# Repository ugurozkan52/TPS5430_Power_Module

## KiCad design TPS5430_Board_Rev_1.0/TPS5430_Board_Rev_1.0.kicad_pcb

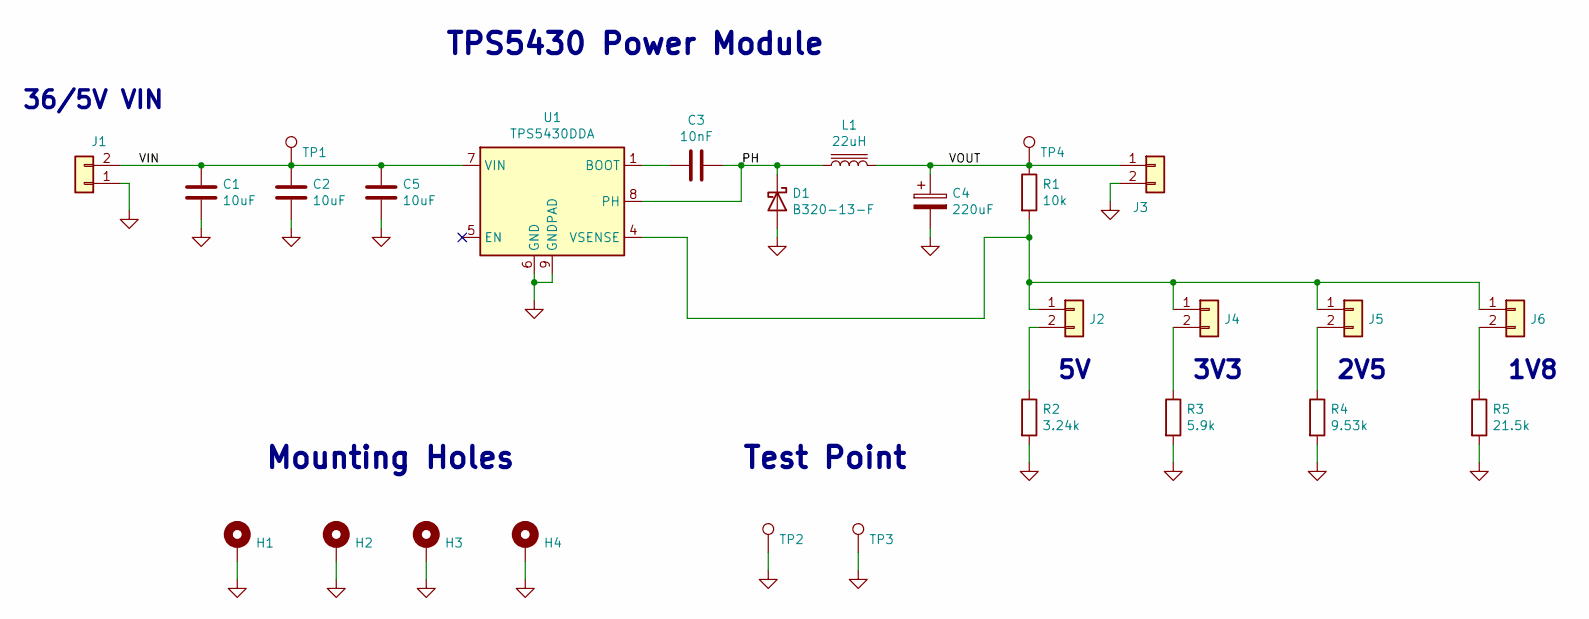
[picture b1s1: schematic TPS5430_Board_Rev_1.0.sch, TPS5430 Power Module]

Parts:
C1, C2, C5: 10uF; C_1210_3225Metric_Pad1.33x2.70mm_HandSolder; Manufacturer Part Number C3225X7R1H106M250AC
C3: 10nF; C_0805_2012Metric_Pad1.18x1.45mm_HandSolder; Manufacturer Part Number CC0805KRX7R9BB103
C4: 220uF; CP_Elec_6.3x5.9; Manufacturer Part Number 6SVPC330M
D1: B320-13-F; D_SMC_Handsoldering; Manufacturer Part Number B320-13-F
H1, H2, H3, H4: MountingHole_Pad; MountingHole_3.2mm_M3_Pad_Via
J1, J3: Conn_01x02; TerminalBlock_Phoenix_MPT-0,5-2-2.54_1x02_P2.54mm_Horizontal; Manufacturer Part Number OSTVN02A150
J2, J4, J5, J6: Conn_01x02; PinHeader_1x02_P2.54mm_Vertical; Manufacturer Part Number 77311-818-02LF
L1: 22uH; L_Wuerth_WE-PD-Typ-LS_Handsoldering; Manufacturer Part Number 7447709220
R1: 10k; R_0805_2012Metric_Pad1.20x1.40mm_HandSolder; Manufacturer Part Number ERJ-6ENF1002V
R2: 3.24k; R_0805_2012Metric_Pad1.20x1.40mm_HandSolder; Manufacturer Part Number ERJ-6ENF3241V
R3: 5.9k; R_0805_2012Metric_Pad1.20x1.40mm_HandSolder; Manufacturer Part Number ERJ-6ENF5901V
R4: 9.53k; R_0805_2012Metric_Pad1.20x1.40mm_HandSolder; Manufacturer Part Number ERJ-6ENF9531V
R5: 21.5k; R_0805_2012Metric_Pad1.20x1.40mm_HandSolder; Manufacturer Part Number ERJ-6ENF2152V
TP1, TP4: TestPoint; TestPoint_THTPad_2.5x2.5mm_Drill1.2mm; Manufacturer Part Number 5000
TP2, TP3: TestPoint; TestPoint_THTPad_2.5x2.5mm_Drill1.2mm; Manufacturer Part Number 5001
U1: TPS5430DDA; TI_SO-PowerPAD-8_ThermalVias; Manufacturer Part Number TPS5430DDAR

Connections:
/PH: C3.1, D1.1 (K), L1.1, U1.8 (PH)
/VIN: C1.1, C2.1, C5.1, J1.2, TP1.1, U1.7 (VIN)
/VOUT: C4.1, J3.1, L1.2, R1.1, TP4.1
GND: C1.2, C2.2, C4.2, C5.2, D1.2 (A), H1.1, H2.1, H3.1, H4.1, J1.1, J3.2, R2.2, R3.2, R4.2, R5.2, TP2.1, TP3.1, U1.6 (GND), U1.9 (GNDPAD)
unnamed: C3.2, U1.1 (BOOT)
unnamed: J2.1, J4.1, J5.1, J6.1, R1.2, U1.4 (VSENSE)
unnamed: J2.2, R2.1
unnamed: J4.2, R3.1
unnamed: J5.2, R4.1
unnamed: J6.2, R5.1

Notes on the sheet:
TPS5430 Power Module
Mounting Holes
Test Point
3V3
2V5
1V8
36/5V VIN

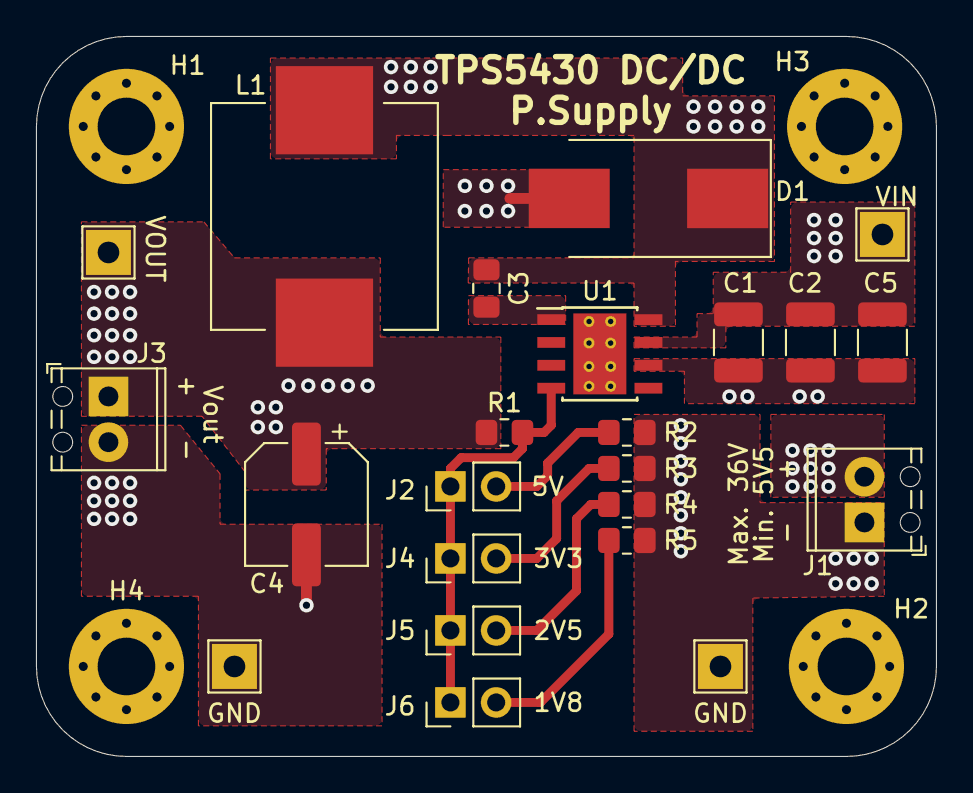
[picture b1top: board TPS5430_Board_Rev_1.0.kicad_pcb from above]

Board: 2 copper layers, 50.0 x 40.0 mm, 27 parts (0 on the bottom side), 10 nets.

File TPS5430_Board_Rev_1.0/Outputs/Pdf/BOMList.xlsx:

Referance | Value | Description | Manufacturer | Manufacturer Part Number | Package | Price | Supply | Supply Part Number | Quantity
C1 | 10uF | CAP CER 10UF 50V X7R 1210 | TDK Corporation | C3225X7R1H106M250AC | 1210 | 0.98 | Digikey | 445-14933-1-ND | 1
C2 | 10uF | CAP CER 10UF 50V X7R 1210 | TDK Corporation | C3225X7R1H106M250AC | 1210 | 0.98 | Digikey | 445-14933-1-ND | 1
C3 | 10nF | CAP CER 10000PF 50V X7R 0805 | Yageo | CC0805KRX7R9BB103 | 805 | 0.1 | Digikey | 311-1136-1-ND | 1
C4 | 220uF | CAP ALUM POLY 330UF 20% 6.3V SMD | Panasonic Electronic Components | 6SVPC330M | SMD | 1.04 | Digikey | P16611CT-ND | 1
C5 | 10uF | CAP CER 10UF 50V X7R 1210 | TDK Corporation | C3225X7R1H106M250AC | 1210 | 0.98 | Digikey | 445-14933-1-ND | 1
D1 | B320-13-F | DIODE SCHOTTKY 20V 3A SMC | Diodes Incorporated | B320-13-F | SMC | 0.47 | Digikey | B320-FDICT-ND | 1
J1 | Conn_01x02 | TERM BLK 2P SIDE ENT 2.54MM PCB | On Shore Technology Inc. | OSTVN02A150 | THT | 0.92 | Digikey | ED10561-ND | 1
J2 | Conn_01x02 | CONN HEADER VERT 2POS 2.54MM | Amphenol ICC (FCI) | 77311-818-02LF | THT | 0.19 | Digikey | 609-4938-ND | 1
J3 | Conn_01x02 | TERM BLK 2P SIDE ENT 2.54MM PCB | On Shore Technology Inc. | OSTVN02A150 | THT | 0.92 | Digikey | ED10561-ND | 1
J4 | Conn_01x02 | CONN HEADER VERT 2POS 2.54MM | Amphenol ICC (FCI) | 77311-818-02LF | THT | 0.19 | Digikey | 609-4938-ND | 1
J5 | Conn_01x02 | CONN HEADER VERT 2POS 2.54MM | Amphenol ICC (FCI) | 77311-818-02LF | THT | 0.19 | Digikey | 609-4938-ND | 1
J6 | Conn_01x02 | CONN HEADER VERT 2POS 2.54MM | Amphenol ICC (FCI) | 77311-818-02LF | THT | 0.19 | Digikey | 609-4938-ND | 1
L1 | 22uH | FIXED IND 22UH 5.3A 28 MOHM SMD | Würth Elektronik | 7447709220 | SMD | 2.41 | Digikey | 732-1243-1-ND | 1
R1 | 10k | RES SMD 10K OHM 1% 1/8W 0805 | Panasonic Electronic Components | ERJ-6ENF1002V | 805 | 0.1 | Digikey | P10.0KCCT-ND | 1
R2 | 3.24k | RES SMD 3.24K OHM 1% 1/8W 0805 | Panasonic Electronic Components | ERJ-6ENF3241V | 805 | 0.1 | Digikey | P3.24KCCT-ND | 1
R3 | 5.9k | RES SMD 5.9K OHM 1% 1/8W 0805 | Panasonic Electronic Components | ERJ-6ENF5901V | 805 | 0.1 | Digikey | P5.90KCCT-ND | 1
R4 | 9.53k | RES SMD 9.53K OHM 1% 1/8W 0805 | Panasonic Electronic Components | ERJ-6ENF9531V | 805 | 0.1 | Digikey | P9.53KCCT-ND | 1
R5 | 21.5k | RES SMD 21.5K OHM 1% 1/8W 0805 | Panasonic Electronic Components | ERJ-6ENF2152V | 805 | 0.1 | Digikey | P21.5KCCT-ND | 1
TP1 | TestPoint | PC TEST POINT MINIATURE RED | Keystone Electronics | 5000 | THT | 0.42 | Digikey | 36-5000-ND | 1
TP2 | TestPoint | PC TEST POINT MINIATURE BLACK | Keystone Electronics | 5001 | THT | 0.42 | Digikey | 36-5001-ND | 1
TP3 | TestPoint | PC TEST POINT MINIATURE BLACK | Keystone Electronics | 5001 | THT | 0.42 | Digikey | 36-5001-ND | 1
TP4 | TestPoint | PC TEST POINT MINIATURE RED | Keystone Electronics | 5000 | THT | 0.42 | Digikey | 36-5000-ND | 1
U1 | TPS5430DDA | IC REG BUCK ADJUSTABLE 3A 8SOPWR | Texas Instruments | TPS5430DDAR | 8SOPWR | 4.08 | Digikey | 296-26988-1-ND | 1

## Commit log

2021-05-02 Project files upload.
